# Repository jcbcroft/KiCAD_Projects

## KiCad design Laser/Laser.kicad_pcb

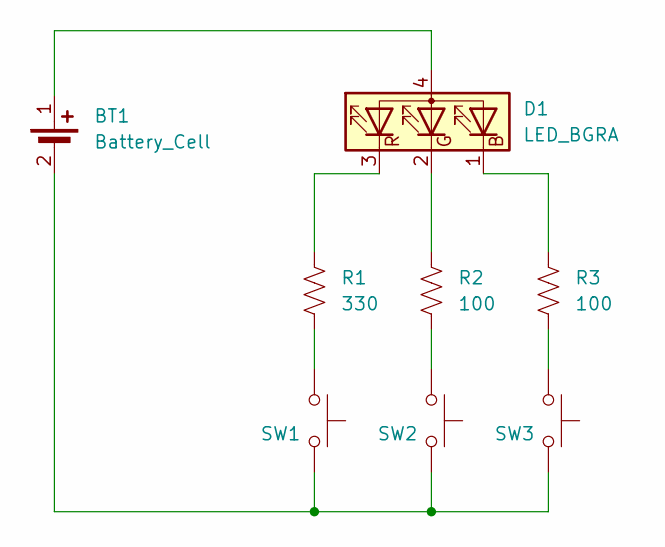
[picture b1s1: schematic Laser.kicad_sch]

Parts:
BT1: Battery_Cell; CR2016; MPN BAT-HLD-002-SMT
D1: LED_BGRA; LED; MPN IN-P32TRRRGB
R1: 330; R_0805_2012Metric; MPN RMCF0805FT330R
R2, R3: 100; R_0805_2012Metric; MPN RMCF0805FT100R
SW1, SW2, SW3: SW_Push; PBTN; MPN PTS526SK15SMTR2 LFS

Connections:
unnamed: BT1.1 (+), D1.4 (A)
unnamed: BT1.2 (-), SW1.2, SW2.2, SW3.2
unnamed: D1.1 (BK), R3.1
unnamed: D1.2 (GK), R2.1
unnamed: D1.3 (RK), R1.1
unnamed: R1.2, SW1.1
unnamed: R2.2, SW2.1
unnamed: R3.2, SW3.1

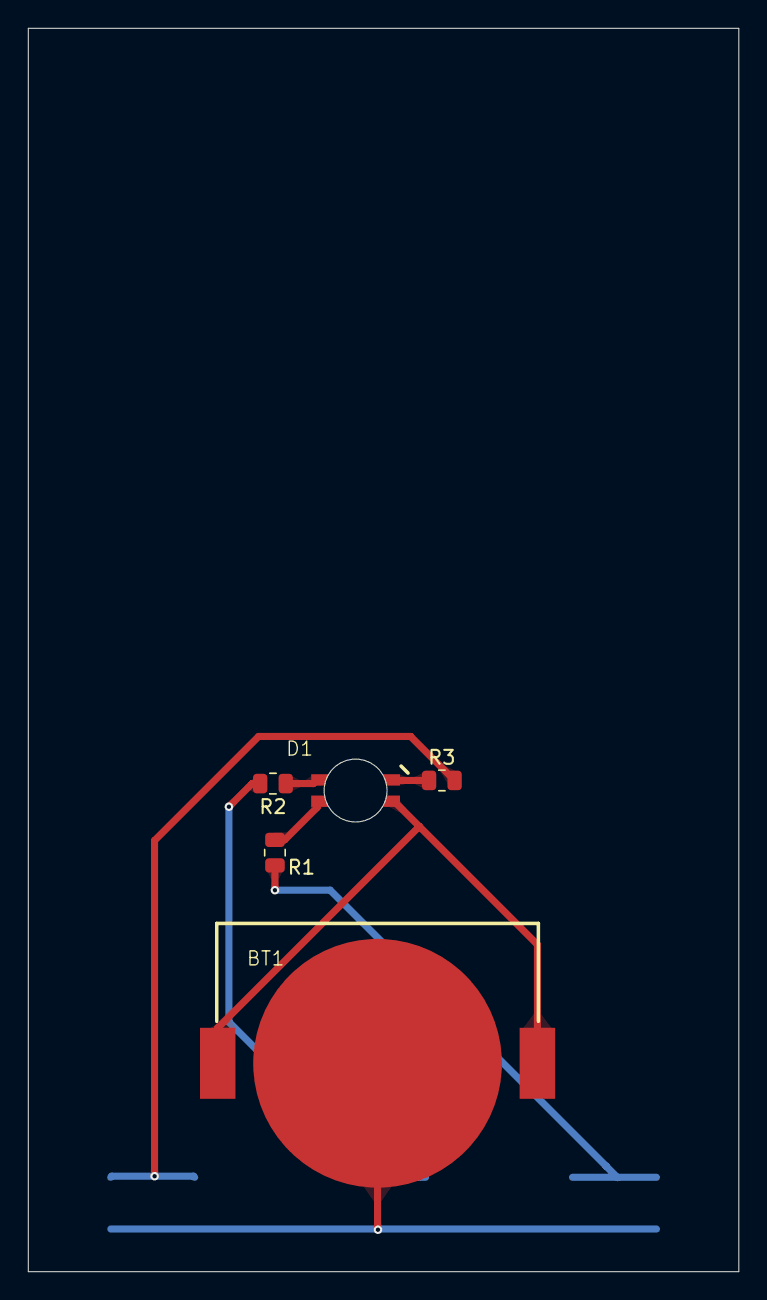
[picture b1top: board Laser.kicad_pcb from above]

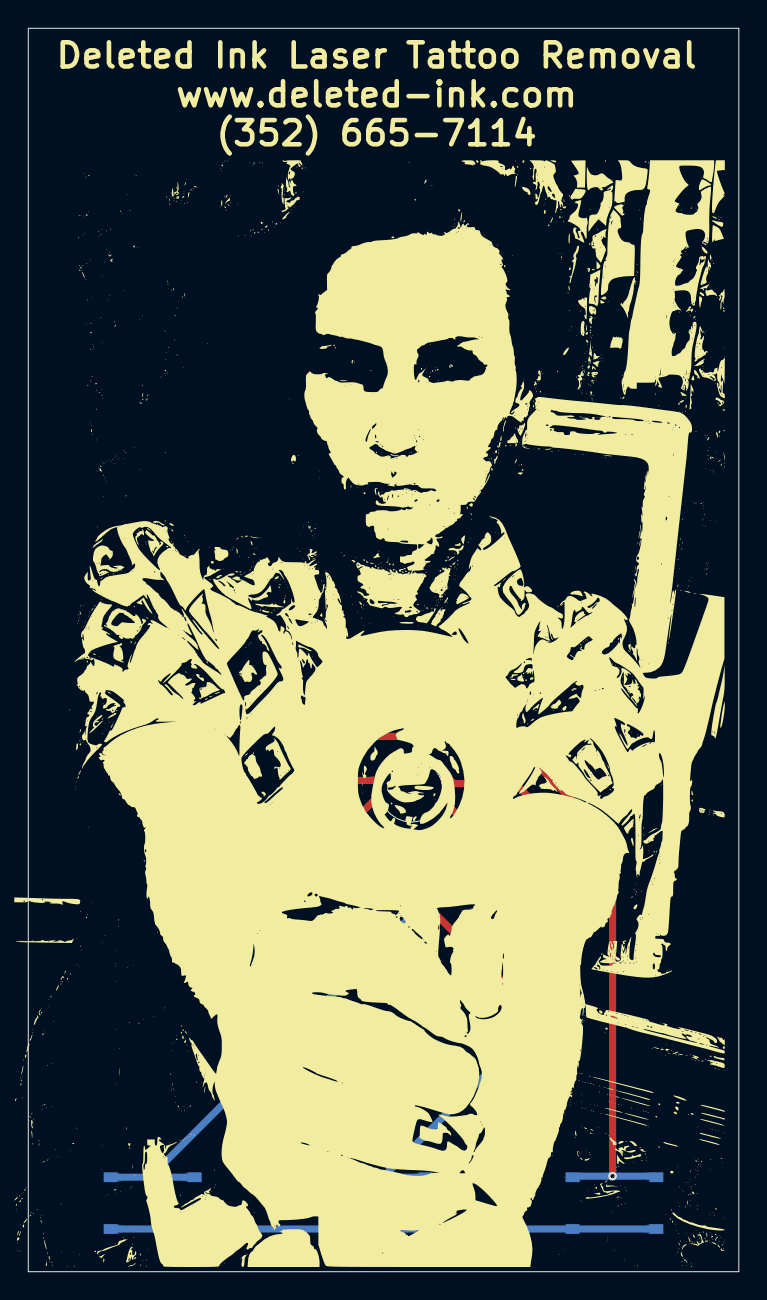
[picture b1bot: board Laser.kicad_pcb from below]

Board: 2 copper layers, 50.8 x 88.9 mm, 8 parts (3 on the bottom side), 8 nets.

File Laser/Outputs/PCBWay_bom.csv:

Designator,Quantity,Value,Footprint,Package,MPN,DNP,Mount_Type,Description,Manufacturer
BT1,1,Battery_Cell,CR2016,,BAT-HLD-002-SMT,,smt,Single-cell battery,TE Connectivity Linx
D1,1,LED_BGRA,LED,,IN-P32TRRRGB,,smt,"RGB LED, blue/green/red/anode",Inolux
R1,1,330,R_0805_2012Metric,,RMCF0805FT330R,,smt,"Resistor, US symbol",Stackpole Electronics Inc
"R2, R3",2,100,R_0805_2012Metric,,RMCF0805FT100R,,smt,"Resistor, US symbol",Stackpole Electronics Inc
"SW1, SW2, SW3",3,SW_Push,PBTN,,PTS526SK15SMTR2 LFS,,smt,"Push button switch, generic, two pins",C&K

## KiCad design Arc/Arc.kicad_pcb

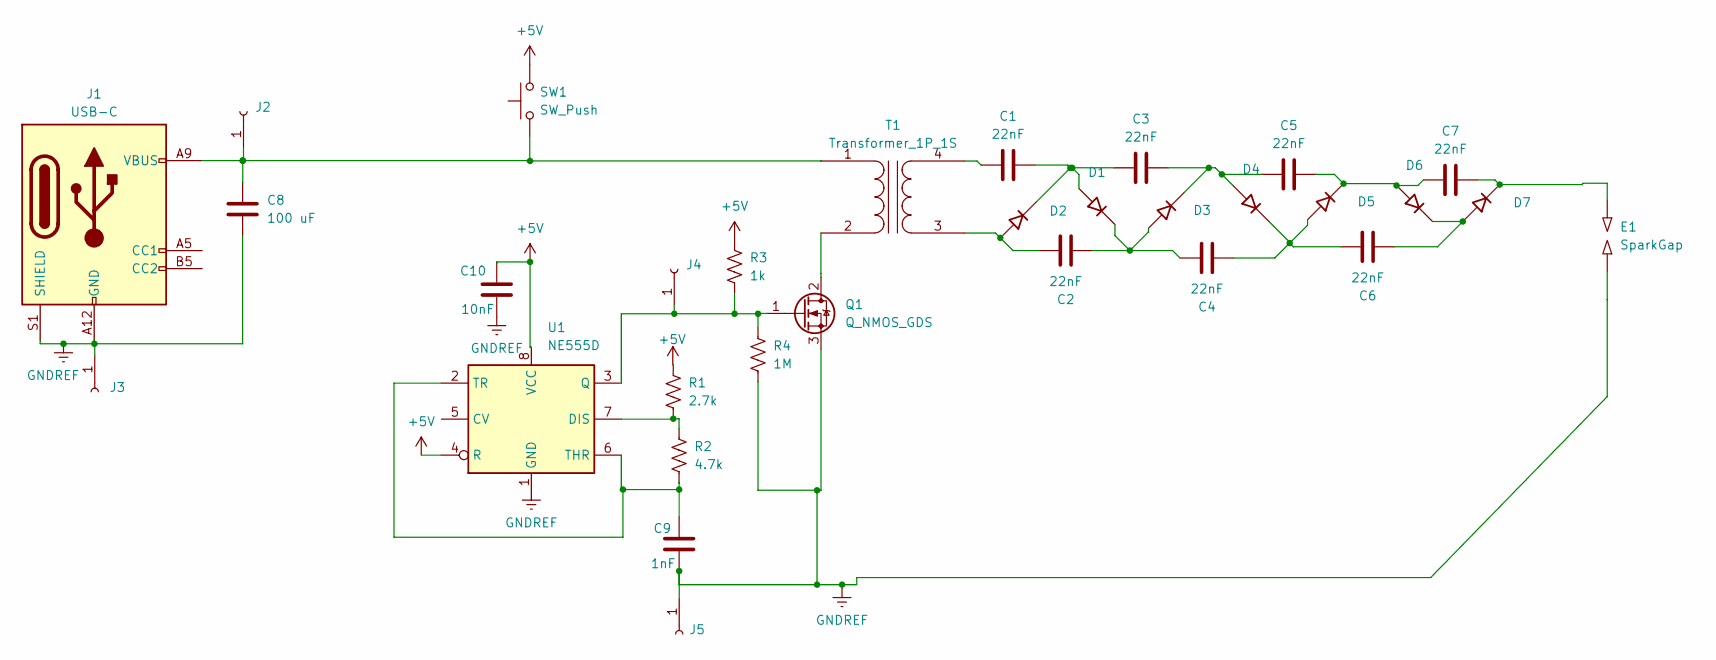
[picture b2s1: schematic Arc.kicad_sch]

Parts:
C1, C2, C3, C4, C5, C6, C7: 22nF; C_1206_3216Metric; MPN C1206C223KDRAC7800
C8: 100 uF; C_1206_3216Metric; MPN GRM31CD80J107MEA8K
C9: 1nF; C_0805_2012Metric; MPN KGM21BCG1H102FT
C10: 10nF; C_0805_2012Metric; MPN C0805C103K5RACTU
D1, D2, D3, D4, D5, D6, D7: D_45deg; D_SOD-123F; MPN 1N4007FL
E1: SparkGap; Spark Gap
J1: USB-C; GCT_USB4135-GF-A_REVA; MPN USB4515-GF-A
J2, J3, J4, J5: Conn_01x01_Socket; 5mm pad
Q1: Q_NMOS_GDS; LFPAK56; MPN PSMN1R2-25YLC,115
R1: 2.7k; R_0805_2012Metric; MPN RMCF0805FT2K70
R2: 4.7k; R_0805_2012Metric; MPN RMCF0805FT4K70
R3: 1k; R_0805_2012Metric; MPN RMCF0805FT1K00
R4: 1M; R_0805_2012Metric; MPN RMCF0805FT1M00
SW1: SW_Push; SW_TL3330AF260QG
T1: Transformer_1P_1S; 53100C; MPN 53100C
U1: NE555D; SOIC-8_3.9x4.9mm_P1.27mm; MPN NE555DR

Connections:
+5V: C10.2, R1.1, R3.1, SW1.2, U1.4 (R), U1.8 (VCC)
GNDREF: C8.1, C9.1, C10.1, E1.2, J1.A12 (GND), J1.B12 (GND), J1.S1 (SHIELD), J5.1, Q1.3 (S), R4.2, U1.1 (GND)
unnamed: C1.2, C3.1, D1.2 (A), D2.1 (K)
unnamed: C2.2, C4.1, D1.1 (K), D3.2 (A)
unnamed: C2.1, D2.2 (A), T1.3 (SA)
unnamed: C3.2, C5.1, D3.1 (K), D4.2 (A)
unnamed: C4.2, C6.1, D4.1 (K), D5.2 (A)
unnamed: C5.2, C7.1, D5.1 (K), D6.2 (A)
unnamed: C6.2, D6.1 (K), D7.2 (A)
unnamed: C7.2, D7.1 (K), E1.1
unnamed: C8.2, J1.A9 (VBUS), J1.B9 (VBUS), J2.1, SW1.1, T1.1 (AA)
unnamed: J4.1, Q1.1 (G), R3.2, R4.1, U1.3 (Q)
unnamed: Q1.2 (D), T1.2 (AB)
unnamed: C1.1, T1.4 (SB)
unnamed: R1.2, R2.1, U1.7 (DIS)
unnamed: C9.2, R2.2, U1.2 (TR), U1.6 (THR)

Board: 2 copper layers, 31 parts (1 on the bottom side), 16 nets, no tracks yet.

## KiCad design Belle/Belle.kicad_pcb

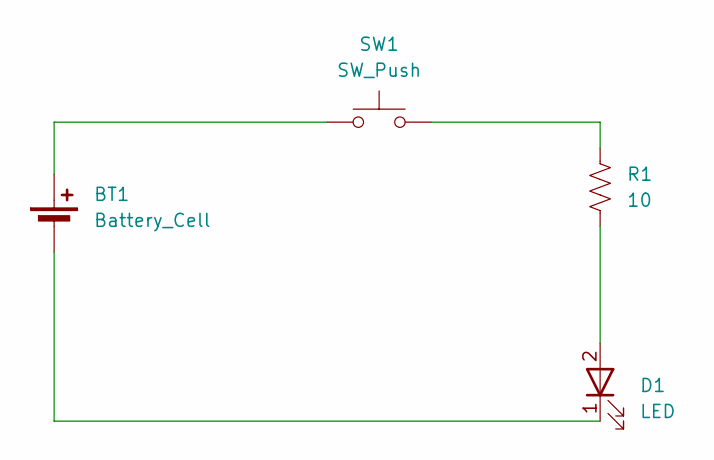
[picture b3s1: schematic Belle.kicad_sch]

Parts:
BT1: Battery_Cell; CR2016; MPN BAT-HLD-002-SMT
D1: LED; LED_C503D-WAN_CRW; MPN C503D-WAN-CCBEB151
R1: 10; R_0805_2012Metric; MPN RMCF0805FT10R0
SW1: SW_Push; EVPBT; MPN EVP-BT6A4A000

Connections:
unnamed: BT1.1 (+), SW1.1
unnamed: BT1.2 (-), D1.1 (K)
unnamed: D1.2 (A), R1.2
unnamed: R1.1, SW1.2

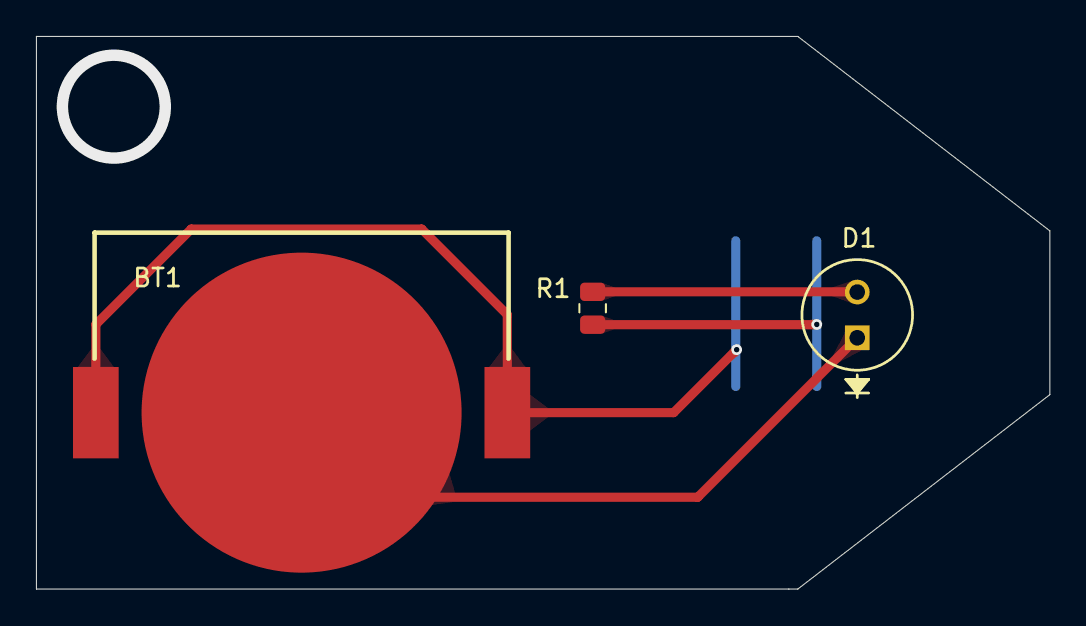
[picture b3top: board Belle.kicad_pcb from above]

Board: 2 copper layers, 56.3 x 30.7 mm, 4 parts (1 on the bottom side), 4 nets.

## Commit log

2024-11-27 Adding Arc project
2024-11-27 Adding component properties
2024-11-27 More component properties. PCB layout.
    Need to fix component pinouts before routing.
2024-11-27 i forgor
2024-11-27 Rearranging stuff
2024-11-27 laser silkscreen footprint
2024-11-28 Laser schematic entry and layout
2024-11-29 Belle Box Board
2024-12-07 Finished Laser and Belle
